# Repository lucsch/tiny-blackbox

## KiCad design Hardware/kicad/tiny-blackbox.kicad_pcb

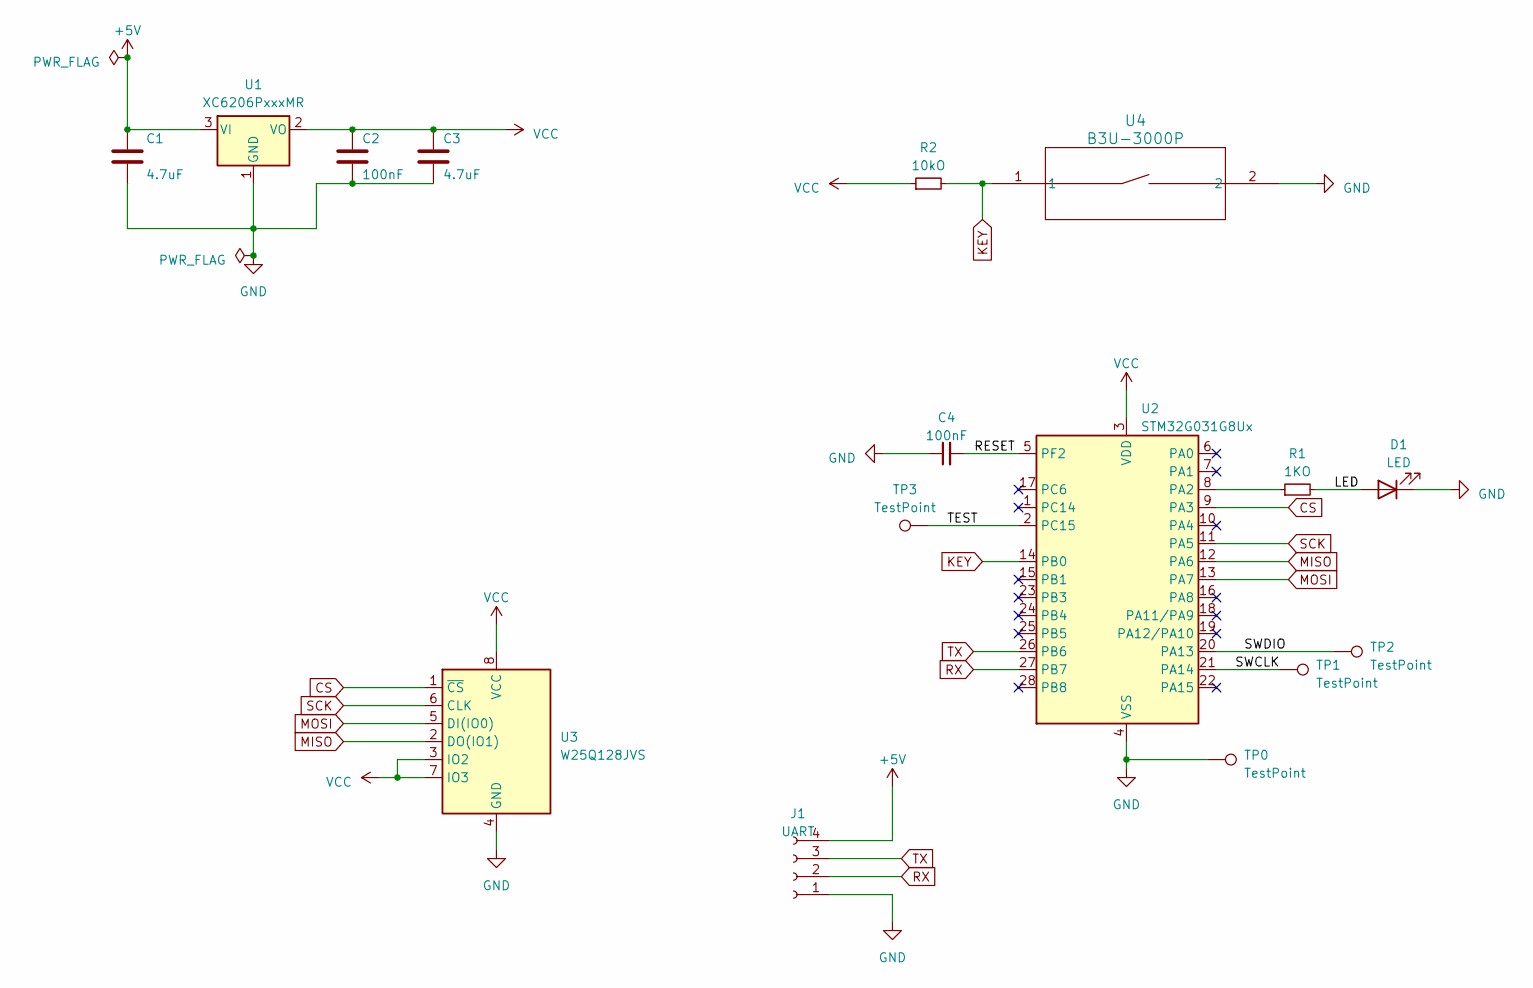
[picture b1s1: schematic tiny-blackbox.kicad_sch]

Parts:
C1, C3: 4.7uF; C_0603_1608Metric
C2, C4: 100nF; C_0603_1608Metric
D1: LED; LED_0603_1608Metric
J1: UART; uart_power_th
R1: 1KO; R_0603_1608Metric
R2: 10kO; R_0603_1608Metric
TP0, TP1, TP2, TP3: TestPoint; TestPoint_Pad_D1.0mm
U1: XC6206PxxxMR; SOT-23-3
U2: STM32G031G8Ux; QFN-28_4x4mm_P0.5mm
U3: W25Q128JVS; SOIC-8_5.23x5.23mm_P1.27mm
U4: B3U-3000P

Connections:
+5V: C1.1, J1.4, U1.3 (VI)
/LED: D1.2 (A), R1.2
/RESET: C4.2, U2.5 (PF2)
/SWCLK: TP1.1, U2.21 (PA14)
/SWDIO: TP2.1, U2.20 (PA13)
/TEST: TP3.1, U2.2 (PC15)
CS: U2.9 (PA3), U3.1 (~CS)
GND: C1.2, C2.2, C3.2, C4.1, D1.1 (K), J1.1, TP0.1, U1.1 (GND), U2.4 (VSS), U3.4 (GND), U4.2
KEY: R2.2, U2.14 (PB0), U4.1
MISO: U2.12 (PA6), U3.2 (DO(IO1))
MOSI: U2.13 (PA7), U3.5 (DI(IO0))
unnamed: R1.1, U2.8 (PA2)
RX: J1.2, U2.27 (PB7)
SCK: U2.11 (PA5), U3.6 (CLK)
TX: J1.3, U2.26 (PB6)
VCC: C2.1, C3.1, R2.1, U1.2 (VO), U2.3 (VDD), U3.3 (IO2), U3.7 (IO3), U3.8 (VCC)

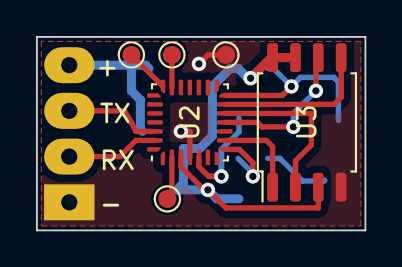
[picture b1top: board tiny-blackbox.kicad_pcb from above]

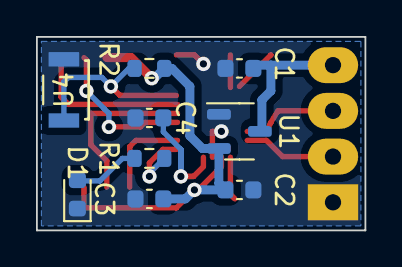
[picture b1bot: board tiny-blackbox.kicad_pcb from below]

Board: 2 copper layers, 18.2 x 10.8 mm, 16 parts (9 on the bottom side), 16 nets.

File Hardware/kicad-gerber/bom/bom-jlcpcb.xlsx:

Comment | Designator | Footprint | LCSC Part Number
4.7uF | C1, C3 | 0603 | C19666
100nF | C2, C4 | 0603 | C14663
LED | D1 | 0603 | C84263
1KO | R1 | 0603 | C21190
10kO | R2 | 0603 | C25804
XC6206PxxxMR | U1 | SOT-23 | C5446
STM32G031G8Ux | U2 | UFQFPN28 | C432211
W25Q128JVS | U3 | SOIC-8 | C190862
B3U-3000P | U4 |  | C963349

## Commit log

2023-04-22 Copying board in kicad
